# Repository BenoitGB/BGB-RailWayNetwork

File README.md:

# BenoitBG

Electronics and Software Projects for Scale Model Railroad

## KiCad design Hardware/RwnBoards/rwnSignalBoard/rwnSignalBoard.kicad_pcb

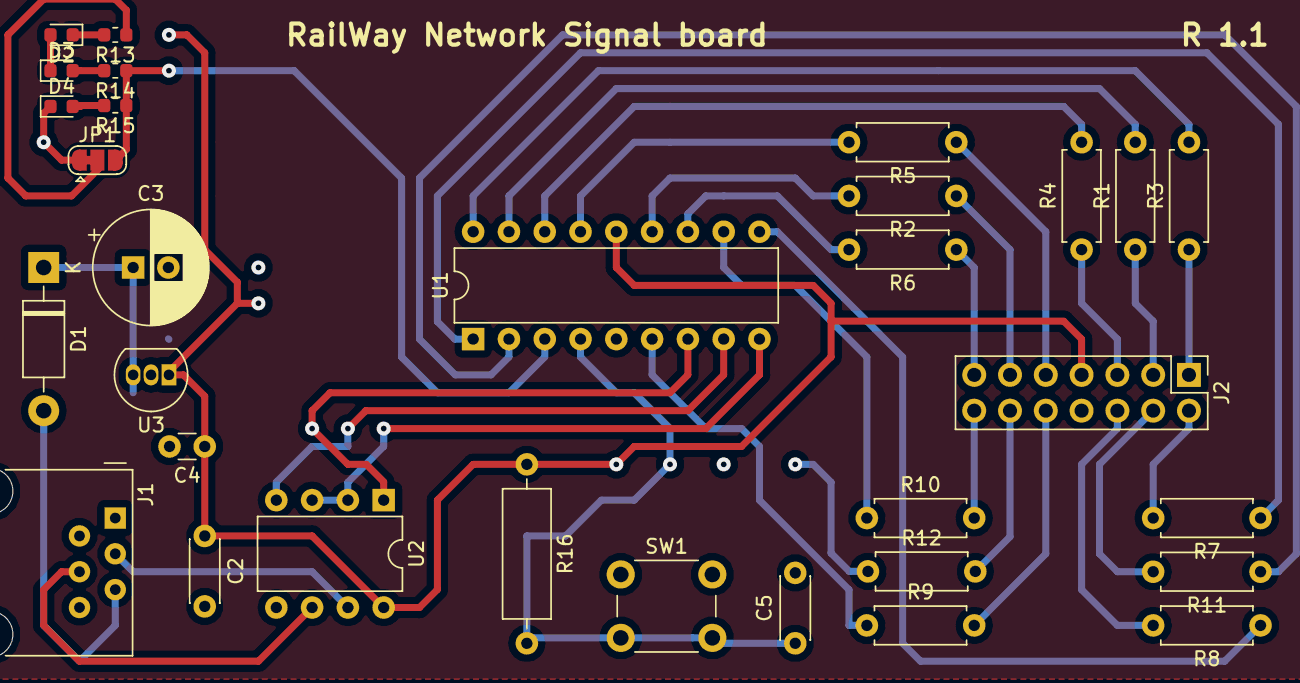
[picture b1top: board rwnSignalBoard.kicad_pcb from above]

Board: 2 copper layers, 31 parts (0 on the bottom side), 38 nets.

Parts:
C2, C5: 100nF; C_Disc_D4.3mm_W1.9mm_P5.00mm
C3: 10µF; CP_Radial_D8.0mm_P2.50mm
C4: 1µf; C_Disc_D3.0mm_W1.6mm_P2.50mm
D1: 1N4001; D_DO-41_SOD81_P10.16mm_Horizontal
D2: Green LED; LED_0603_1608Metric
D3: Yellow LED; LED_0603_1608Metric
D4: Red LED; LED_0603_1608Metric
J1: RJ12; RJ12_Amphenol_54601
J2: Conn_02x07_Odd_Even; PinHeader_2x07_P2.54mm_Vertical
JP1: SolderJumper_3_Open; SolderJumper-3_P1.3mm_Bridged12_RoundedPad1.0x1.5mm
R1, R2, R3, R4, R5, R6, R7, R8, R9, R10, R11, R12: R; R_Axial_DIN0207_L6.3mm_D2.5mm_P7.62mm_Horizontal
R13, R14, R15: 103; R_0603_1608Metric
R16: 10k; R_Axial_DIN0309_L9.0mm_D3.2mm_P12.70mm_Horizontal
SW1: SW_Push; SW_PUSH_6mm
U1: PIC16F628A-IP; DIP-18_W7.62mm
U2: MAX3483; DIP-8_W7.62mm
U3: LM78L05_TO92; TO-92_Inline

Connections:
+12V: C3.1, D1.1, U3.3
/AV: R11.1, U1.2
/C-CV: R9.1, U1.6
/ID1: R2.2, U1.13
/ID2: R6.2, U1.12
/ID3: R10.1, U1.11
/MA: R5.2, U1.15
/OE: R1.2, U1.17
/R: R7.1, U1.1
/RR: R3.2, U1.18
/RS485Block/A: J1.4, U2.6
/RS485Block/B: J1.3, U2.7
/RS485Block/RWRS: U1.9, U2.2, U2.3
/RS485Block/RX: U1.7, U2.1
/RS485Block/TX: U1.8, U2.4
/S: R8.1, U1.10
/VL: R4.2, U1.16
/rwnResetBlock/RESET: C5.1, R16.2, SW1.2, U1.4
/rwnSLIBlock/STATUS0: JP1.3, R14.1, R15.1, U1.3
GND: C2.2, C3.2, C4.2, C5.2, D2.2, D3.1, D4.1, J1.2, JP1.1, SW1.1, U1.5, U2.5, U3.2
unnamed: D1.2, J1.5
unnamed: D2.1, R13.2
unnamed: D3.2, R14.2
unnamed: D4.2, R15.2
unnamed: J2.1, R3.1
unnamed: J2.2, R7.2
unnamed: J2.3, R1.1
unnamed: J2.4, R11.2
unnamed: J2.5, R4.1
unnamed: J2.6, R8.2
unnamed: J2.9, R5.1
unnamed: J2.10, R9.2
unnamed: J2.11, R2.1
unnamed: J2.12, R12.2
unnamed: J2.13, R6.1
unnamed: J2.14, R10.2
unnamed: JP1.2, R13.1
VCC: C2.1, C4.1, J2.7, R16.1, U1.14, U2.8, U3.1

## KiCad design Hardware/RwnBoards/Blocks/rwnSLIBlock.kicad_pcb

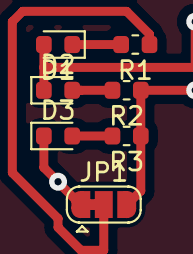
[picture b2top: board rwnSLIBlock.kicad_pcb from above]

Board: 2 copper layers, 7 parts (0 on the bottom side), 7 nets.

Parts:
D1: Green LED; LED_0603_1608Metric
D2: Yellow LED; LED_0603_1608Metric
D3: Red LED; LED_0603_1608Metric
JP1: SolderJumper_3_Open; SolderJumper-3_P1.3mm_Bridged12_RoundedPad1.0x1.5mm
R1, R2, R3: 103; R_0603_1608Metric

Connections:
/STATUS0: JP1.3, R2.1, R3.1
/STATUS1: D1.2, D2.1
GND: D3.1, JP1.1
unnamed: D1.1, R1.2
unnamed: D2.2, R2.2
unnamed: D3.2, R3.2
unnamed: JP1.2, R1.1

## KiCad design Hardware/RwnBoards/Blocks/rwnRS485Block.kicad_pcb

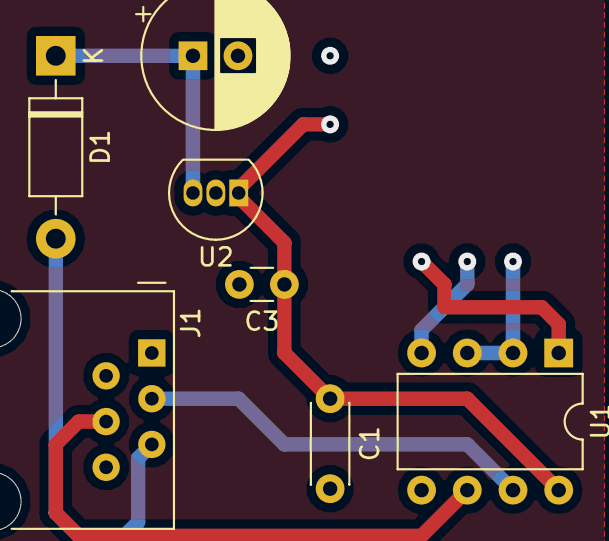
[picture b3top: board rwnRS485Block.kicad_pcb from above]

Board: 2 copper layers, 7 parts (0 on the bottom side), 7 nets.

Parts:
C1: 100nF; C_Disc_D4.3mm_W1.9mm_P5.00mm
C2: 10µF; CP_Radial_D8.0mm_P2.50mm
C3: 1µf; C_Disc_D3.0mm_W1.6mm_P2.50mm
D1: 1N4001; D_DO-41_SOD81_P10.16mm_Horizontal
J1: RJ12; RJ12_Amphenol_54601
U1: MAX3483; DIP-8_W7.62mm
U2: LM78L05_TO92; TO-92_Inline

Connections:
+12V: C2.1, D1.1, U2.3
/A: J1.4, U1.6
/B: J1.3, U1.7
/RWRS: U1.2, U1.3
GND: C1.2, C2.2, C3.2, J1.2, U1.5, U2.2
unnamed: D1.2, J1.5
VCC: C1.1, C3.1, U1.8, U2.1

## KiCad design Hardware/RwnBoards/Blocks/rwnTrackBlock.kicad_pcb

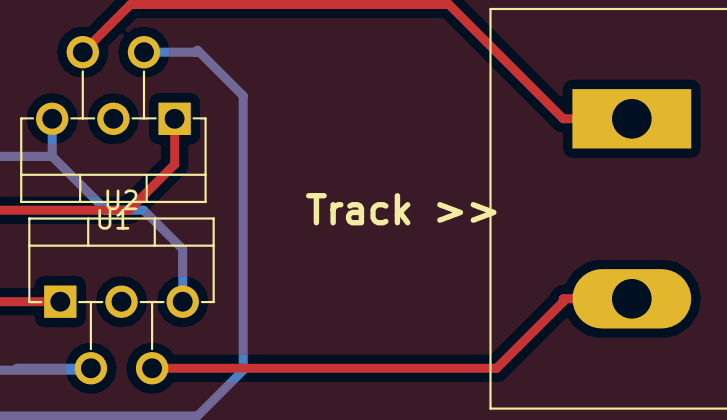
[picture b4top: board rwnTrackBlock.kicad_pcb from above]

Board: 2 copper layers, 3 parts (0 on the bottom side), 5 nets.

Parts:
J1: Track; TerminalBlock_Dinkle_DT-55-B01X-02_P10.00mm
U1, U2: UDN2951Z; TO-220-5_P3.4x3.7mm_StaggerEven_Lead3.8mm_Vertical

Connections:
+12V: U1.1, U2.1
/PWM: U1.5, U2.5
GND: U1.3, U2.3
unnamed: J1.1, U1.4
unnamed: J1.2, U2.4

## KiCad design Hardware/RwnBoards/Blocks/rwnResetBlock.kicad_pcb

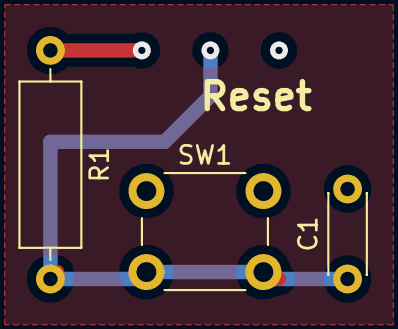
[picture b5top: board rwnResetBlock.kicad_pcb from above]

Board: 2 copper layers, 3 parts (0 on the bottom side), 2 nets.

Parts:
C1: 100nF; C_Disc_D4.3mm_W1.9mm_P5.00mm
R1: 10k; R_Axial_DIN0309_L9.0mm_D3.2mm_P12.70mm_Horizontal
SW1: SW_Push; SW_PUSH_6mm

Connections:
/RESET: C1.1, R1.2, SW1.2
GND: C1.2, SW1.1

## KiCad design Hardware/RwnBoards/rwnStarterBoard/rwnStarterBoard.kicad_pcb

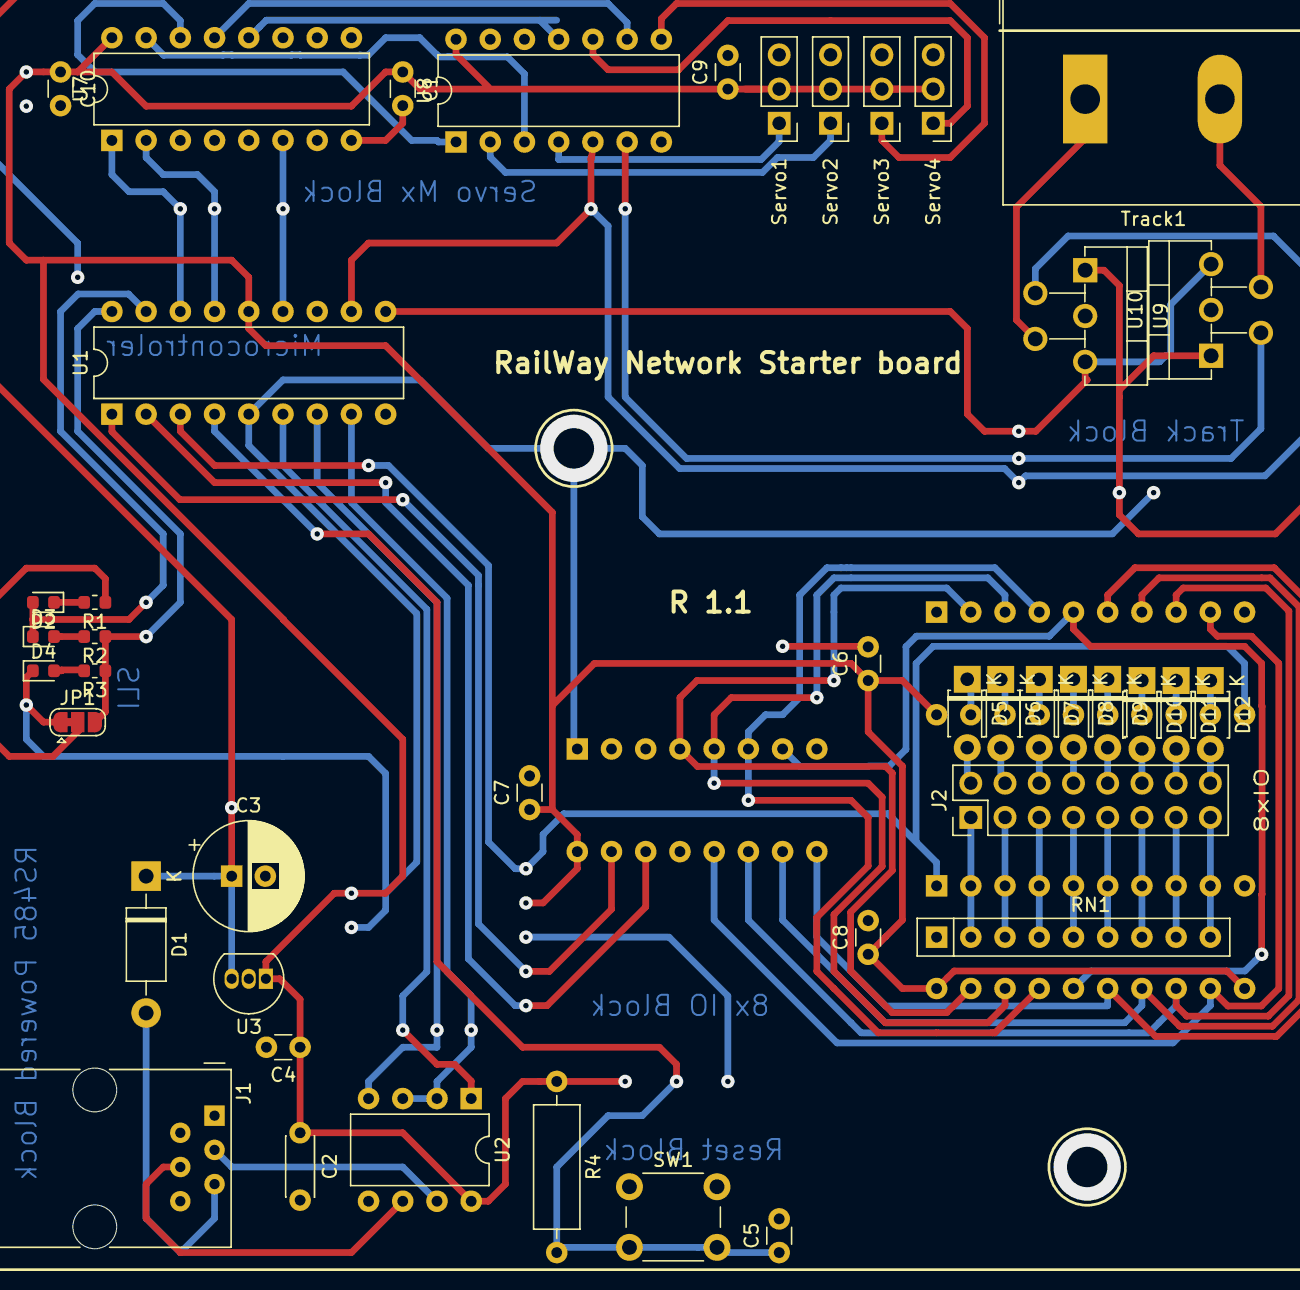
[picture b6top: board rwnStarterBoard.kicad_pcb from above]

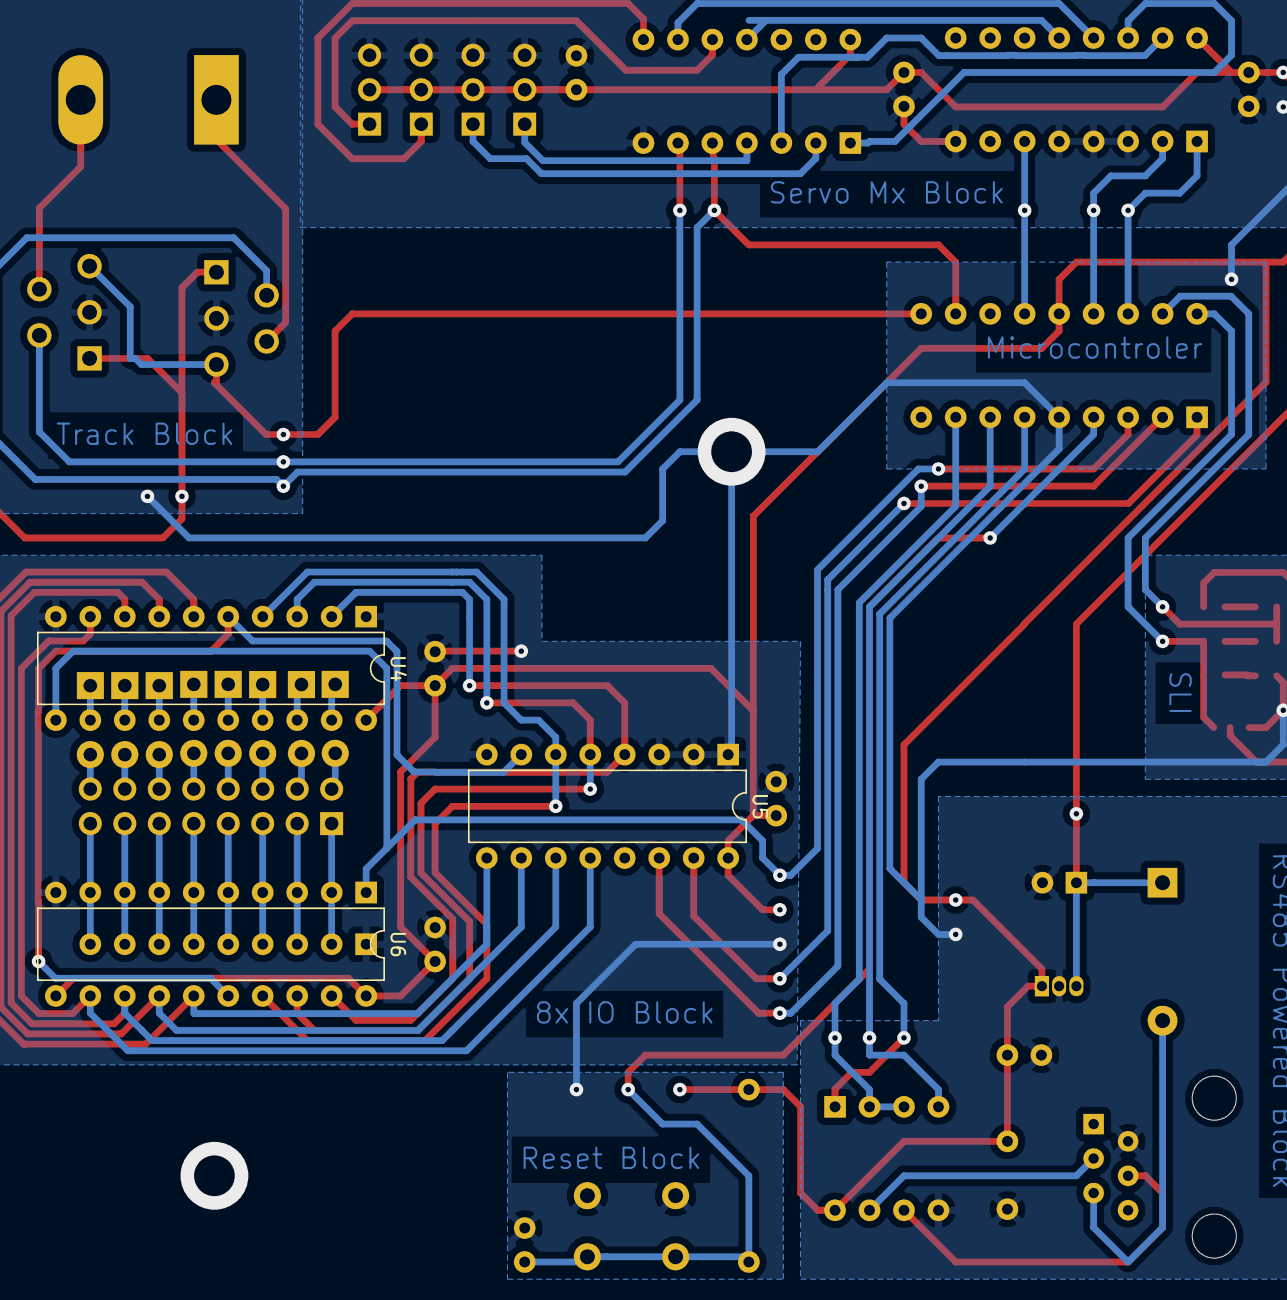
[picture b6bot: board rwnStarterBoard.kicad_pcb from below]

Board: 2 copper layers, 46 parts (3 on the bottom side), 67 nets.

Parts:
C1, C5, C9, C10: 100nF; C_Disc_D3.0mm_W1.6mm_P2.50mm
C2: 100nF; C_Disc_D4.3mm_W1.9mm_P5.00mm
C3: 10µF; CP_Radial_D8.0mm_P2.50mm
C4: 1µf; C_Disc_D3.0mm_W1.6mm_P2.50mm
C6, C7, C8: 100nf; C_Disc_D3.0mm_W1.6mm_P2.50mm
D1: 1N4001; D_DO-41_SOD81_P10.16mm_Horizontal
D2: Green LED; LED_0603_1608Metric
D3: Yellow LED; LED_0603_1608Metric
D4: Red LED; LED_0603_1608Metric
D5, D6, D7, D8, D9, D10, D11, D12: D; D_T-1_P5.08mm_Horizontal
J1: RJ12; RJ12_Amphenol_54601
J2: Conn_IO; PinHeader_2x08_P2.54mm_Vertical
JP1: SolderJumper_3_Open; SolderJumper-3_P1.3mm_Bridged12_RoundedPad1.0x1.5mm
R1, R2, R3: 103; R_0603_1608Metric
R4: 10k; R_Axial_DIN0309_L9.0mm_D3.2mm_P12.70mm_Horizontal
RN1: 1k; R_Array_SIP9
SW1: SW_Push; SW_PUSH_6mm
Servo1, Servo2, Servo3, Servo4: Servo; PinHeader_1x03_P2.54mm_Vertical
Track1: Track; TerminalBlock_Dinkle_DT-55-B01X-02_P10.00mm
U1: PIC16F628A-IP; DIP-18_W7.62mm
U2: MAX3483; DIP-8_W7.62mm
U3: LM78L05_TO92; TO-92_Inline
U4, U6: 74LS573; DIP-20_W7.62mm
U5: PCF8574; DIP-16_W7.62mm
U7: 74LS138; DIP-16_W7.62mm
U8: 74LS05; DIP-14_W7.62mm
U9, U10: UDN2951Z; TO-220-5_P3.4x3.7mm_StaggerEven_Lead3.8mm_Vertical

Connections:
+12V: C3.1, D1.1, U3.3, U9.1, U10.1
/RS485Block/A: J1.4, U2.6
/RS485Block/B: J1.3, U2.7
/RS485Block/RWRS: U1.8, U2.2, U2.3
/RS485Block/RX: U1.6, U2.1
/RS485Block/TX: U1.7, U2.4
/rwnI2CESBlock/IO: U1.3, U4.11, U6.1
/rwnI2CESBlock/IO0: U4.2, U5.4, U6.19
/rwnI2CESBlock/IO1: U4.3, U5.5, U6.18
/rwnI2CESBlock/IO2: U4.4, U5.6, U6.17
/rwnI2CESBlock/IO3: U4.5, U5.7, U6.16
/rwnI2CESBlock/IO4: U4.6, U5.9, U6.15
/rwnI2CESBlock/IO5: U4.7, U5.10, U6.14
/rwnI2CESBlock/IO6: U4.8, U5.11, U6.13
/rwnI2CESBlock/IO7: U4.9, U5.12, U6.12
/rwnI2CESBlock/SCL: U1.2, U5.14
/rwnI2CESBlock/SDA: U1.1, U5.15
/rwnResetBlock/RESET: C5.1, R4.2, SW1.2, U1.4
/rwnSLIBlock/STATUS0: JP1.3, R2.1, R3.1, U1.18
/rwnSLIBlock/STATUS1: D2.2, D3.1, U1.17
/rwnServoMxBlock/A0: U1.16, U7.1
/rwnServoMxBlock/A1: U1.15, U7.2
/rwnServoMxBlock/CMD: U1.13, U7.6
/rwnTrackBlock/-DIR: U8.6, U10.2
/rwnTrackBlock/DIR: U1.11, U8.5, U9.2
/rwnTrackBlock/PWM: U1.10, U9.5, U10.5
GND: C1.2, C2.2, C3.2, C4.2, C5.2, C6.2, C7.2, C8.2, C9.2, C10.2, D4.1, J1.2, JP1.1, RN1.1, SW1.1, Servo1.3, Servo2.3, Servo3.3, Servo4.3, U1.5, U2.5, U3.2, U4.1, U4.10, U5.1, U5.2, U5.3, U5.8, U6.10, U7.3, U7.4, U7.5, U7.8, U8.7, U9.3, U10.3
unnamed: D1.2, J1.5
unnamed: D2.1, R1.2
unnamed: D3.2, R2.2
unnamed: D4.2, R3.2
unnamed: D5.1, U4.19
unnamed: D5.2, J2.2
unnamed: D6.1, U4.18
unnamed: D6.2, J2.4
unnamed: D7.1, U4.17
unnamed: D7.2, J2.6
unnamed: D8.1, U4.16
unnamed: D8.2, J2.8
unnamed: D9.1, U4.15
unnamed: D9.2, J2.10
unnamed: D10.1, U4.14
unnamed: D10.2, J2.12
unnamed: D11.1, U4.13
unnamed: D11.2, J2.14
unnamed: D12.1, U4.12
unnamed: D12.2, J2.16
unnamed: J2.1, RN1.2, U6.2
unnamed: J2.3, RN1.3, U6.3
unnamed: J2.5, RN1.4, U6.4
unnamed: J2.7, RN1.5, U6.5
unnamed: J2.9, RN1.6, U6.6
unnamed: J2.11, RN1.7, U6.7
unnamed: J2.13, RN1.8, U6.8
unnamed: J2.15, RN1.9, U6.9
unnamed: JP1.2, R1.1
unnamed: Servo1.1, U8.4
unnamed: Servo2.1, U8.2
unnamed: Servo3.1, U8.8
unnamed: Servo4.1, U8.10
unnamed: Track1.1, U9.4
unnamed: Track1.2, U10.4
unnamed: U7.12, U8.11
unnamed: U7.13, U8.9
unnamed: U7.14, U8.1
unnamed: U7.15, U8.3
VCC: C1.1, C2.1, C4.1, C6.1, C7.1, C8.1, C9.1, C10.1, R4.1, Servo1.2, Servo2.2, Servo3.2, Servo4.2, U1.14, U2.8, U3.1, U4.20, U5.16, U6.11, U6.20, U7.16, U8.14

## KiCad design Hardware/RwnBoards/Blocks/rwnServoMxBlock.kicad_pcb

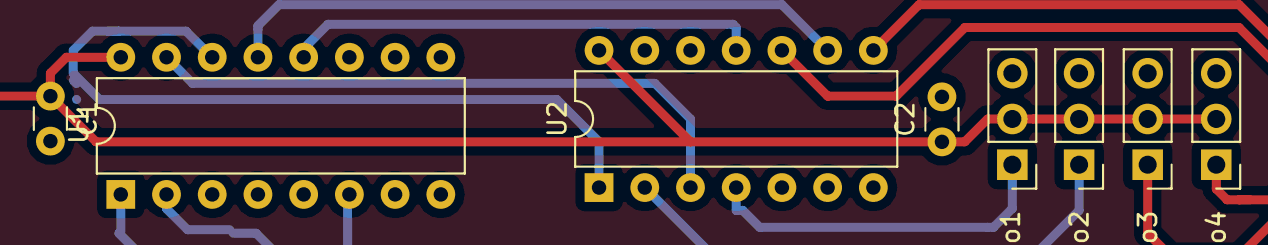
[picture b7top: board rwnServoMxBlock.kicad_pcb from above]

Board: 2 copper layers, 8 parts (0 on the bottom side), 10 nets.

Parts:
C1, C2: 100nF; C_Disc_D3.0mm_W1.6mm_P2.50mm
Servo1, Servo2, Servo3, Servo4: Servo; PinHeader_1x03_P2.54mm_Vertical
U1: 74LS138; DIP-16_W7.62mm
U2: 74LS05; DIP-14_W7.62mm

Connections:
GND: C1.2, C2.2, Servo1.3, Servo2.3, Servo3.3, Servo4.3, U1.3, U1.4, U1.5, U1.8, U2.7
unnamed: Servo1.1, U2.4
unnamed: Servo2.1, U2.2
unnamed: Servo3.1, U2.8
unnamed: Servo4.1, U2.10
unnamed: U1.12, U2.11
unnamed: U1.13, U2.9
unnamed: U1.14, U2.1
unnamed: U1.15, U2.3
VCC: C1.1, C2.1, Servo1.2, Servo2.2, Servo3.2, Servo4.2, U1.16, U2.14

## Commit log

2018-08-30 Add basic block shematics and boards
2018-09-08 -Reduce "block_statut_led" layout size for 3D preview -Add images as wiki ,gitPages ressources
2018-09-08 wrong test
2018-09-08 hide gitPages ressources
2018-09-08 Set theme jekyll-theme-slate
2018-09-30 add picture for "dimming effect" wiki page
2018-10-21 Kicad migration
